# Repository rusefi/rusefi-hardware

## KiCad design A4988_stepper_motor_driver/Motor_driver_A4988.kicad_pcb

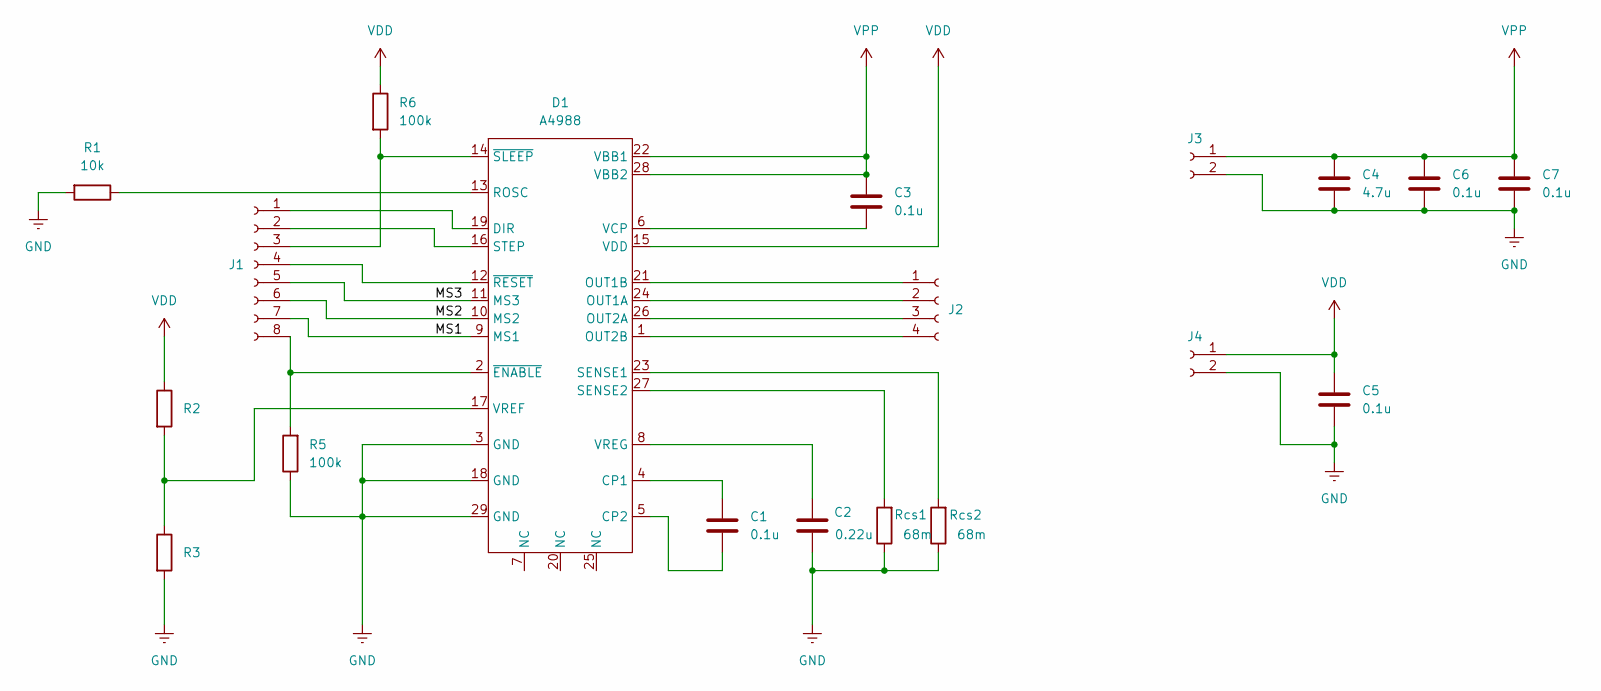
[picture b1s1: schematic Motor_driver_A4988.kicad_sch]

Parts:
C1, C3, C5, C6, C7: 0.1u; C_0603_1608Metric
C2: 0.22u; C_0603_1608Metric
C4: 4.7u; C_1206_3216Metric
D1: A4988; QFN-28-1EP_5x5mm_P0.5mm_EP3.35x3.35mm
J1: Conn_01x08_Socket; PinHeader_1x08_P2.54mm_Vertical
J2: Conn_01x04_Socket; PinHeader_1x04_P2.54mm_Vertical
J3, J4: Conn_01x02_Socket; PinHeader_1x02_P2.54mm_Vertical
R1: 10k; R_0603_1608Metric
R2, R3: R_0603_1608Metric
R5, R6: 100k; R_0603_1608Metric
Rcs1, Rcs2: 68m; R_1206_3216Metric

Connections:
/MS1: D1.9 (MS1), J1.7
/MS2: D1.10 (MS2), J1.6
/MS3: D1.11 (MS3), J1.5
GNDREF: C2.2, C4.2, C5.2, C6.2, C7.2, D1.3 (GND), D1.18 (GND), D1.29 (GND), J3.2, J4.2, R1.2, R3.2, R5.1, Rcs1.1, Rcs2.1
unnamed: C1.1, D1.4 (CP1)
unnamed: C1.2, D1.5 (CP2)
unnamed: D1.19 (DIR), J1.1
unnamed: D1.24 (OUT1A), J2.2
unnamed: D1.21 (OUT1B), J2.1
unnamed: D1.26 (OUT2A), J2.3
unnamed: D1.1 (OUT2B), J2.4
unnamed: D1.13 (ROSC), R1.1
unnamed: D1.23 (SENSE1), Rcs2.2
unnamed: D1.27 (SENSE2), Rcs1.2
unnamed: D1.16 (STEP), J1.2
unnamed: C3.2, D1.6 (VCP)
unnamed: D1.17 (VREF), R2.2, R3.1
unnamed: C2.1, D1.8 (VREG)
unnamed: D1.2 (~ENABLE), J1.8, R5.2
unnamed: D1.12 (~RESET), J1.4
unnamed: D1.14 (~SLEEP), J1.3, R6.2
VDD: C5.1, D1.15 (VDD), J4.1, R2.1, R6.1
VPP: C3.1, C4.1, C6.1, C7.1, D1.22 (VBB1), D1.28 (VBB2), J3.1

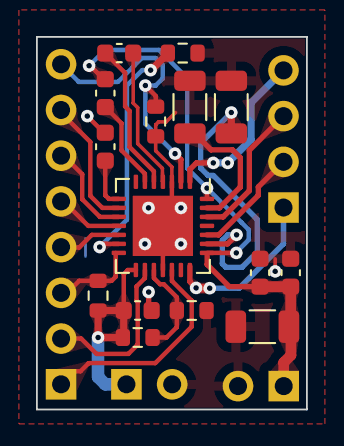
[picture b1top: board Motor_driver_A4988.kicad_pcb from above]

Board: 2 copper layers, 15.0 x 20.7 mm, 20 parts (1 on the bottom side), 23 nets.

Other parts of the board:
G?: LOGO

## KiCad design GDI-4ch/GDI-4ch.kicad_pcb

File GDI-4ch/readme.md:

[User Documentation](https://github.com/rusefi/rusefi/wiki/GDI4)

https://rusefi.com/forum/viewtopic.php?f=4&t=1337

## JLCPCB assembly

**DNP** means “do not place”: JLC will not install that whole group of parts. You solder them yourself later, or you fix the order before manufacturing so those spots get real parts from the JLC library. The DNP groups are listed in **`gerber/rev. c/GDI-4ch.csv`** — resistors **R1, R37, R44, R55, R80, R81, R82, R83, R87, R89, R90, R121** and **R5, R28, R30, R32, R117, R118, R119, R120**.

**If JLC is assembling the board for you:** In the online assembly step, check that you actually selected a part for every line you care about. Parts people often forget to turn on: diodes **D5 and D6** (JLC part number **C8678**), and the **0805 jumper pads** that share one line in the parts list (often **C17477** in **`gerber/rev. d/bom.csv`**). File names and lists change between revisions—use the **`gerber/`** folder that matches the board files you ordered.

## HOWTO Update Firmware

UART route https://www.adafruit.com/product/954

See also https://github.com/rusefi/rusefi/blob/master/firmware/controllers/lua/examples/gdi4-communication.lua

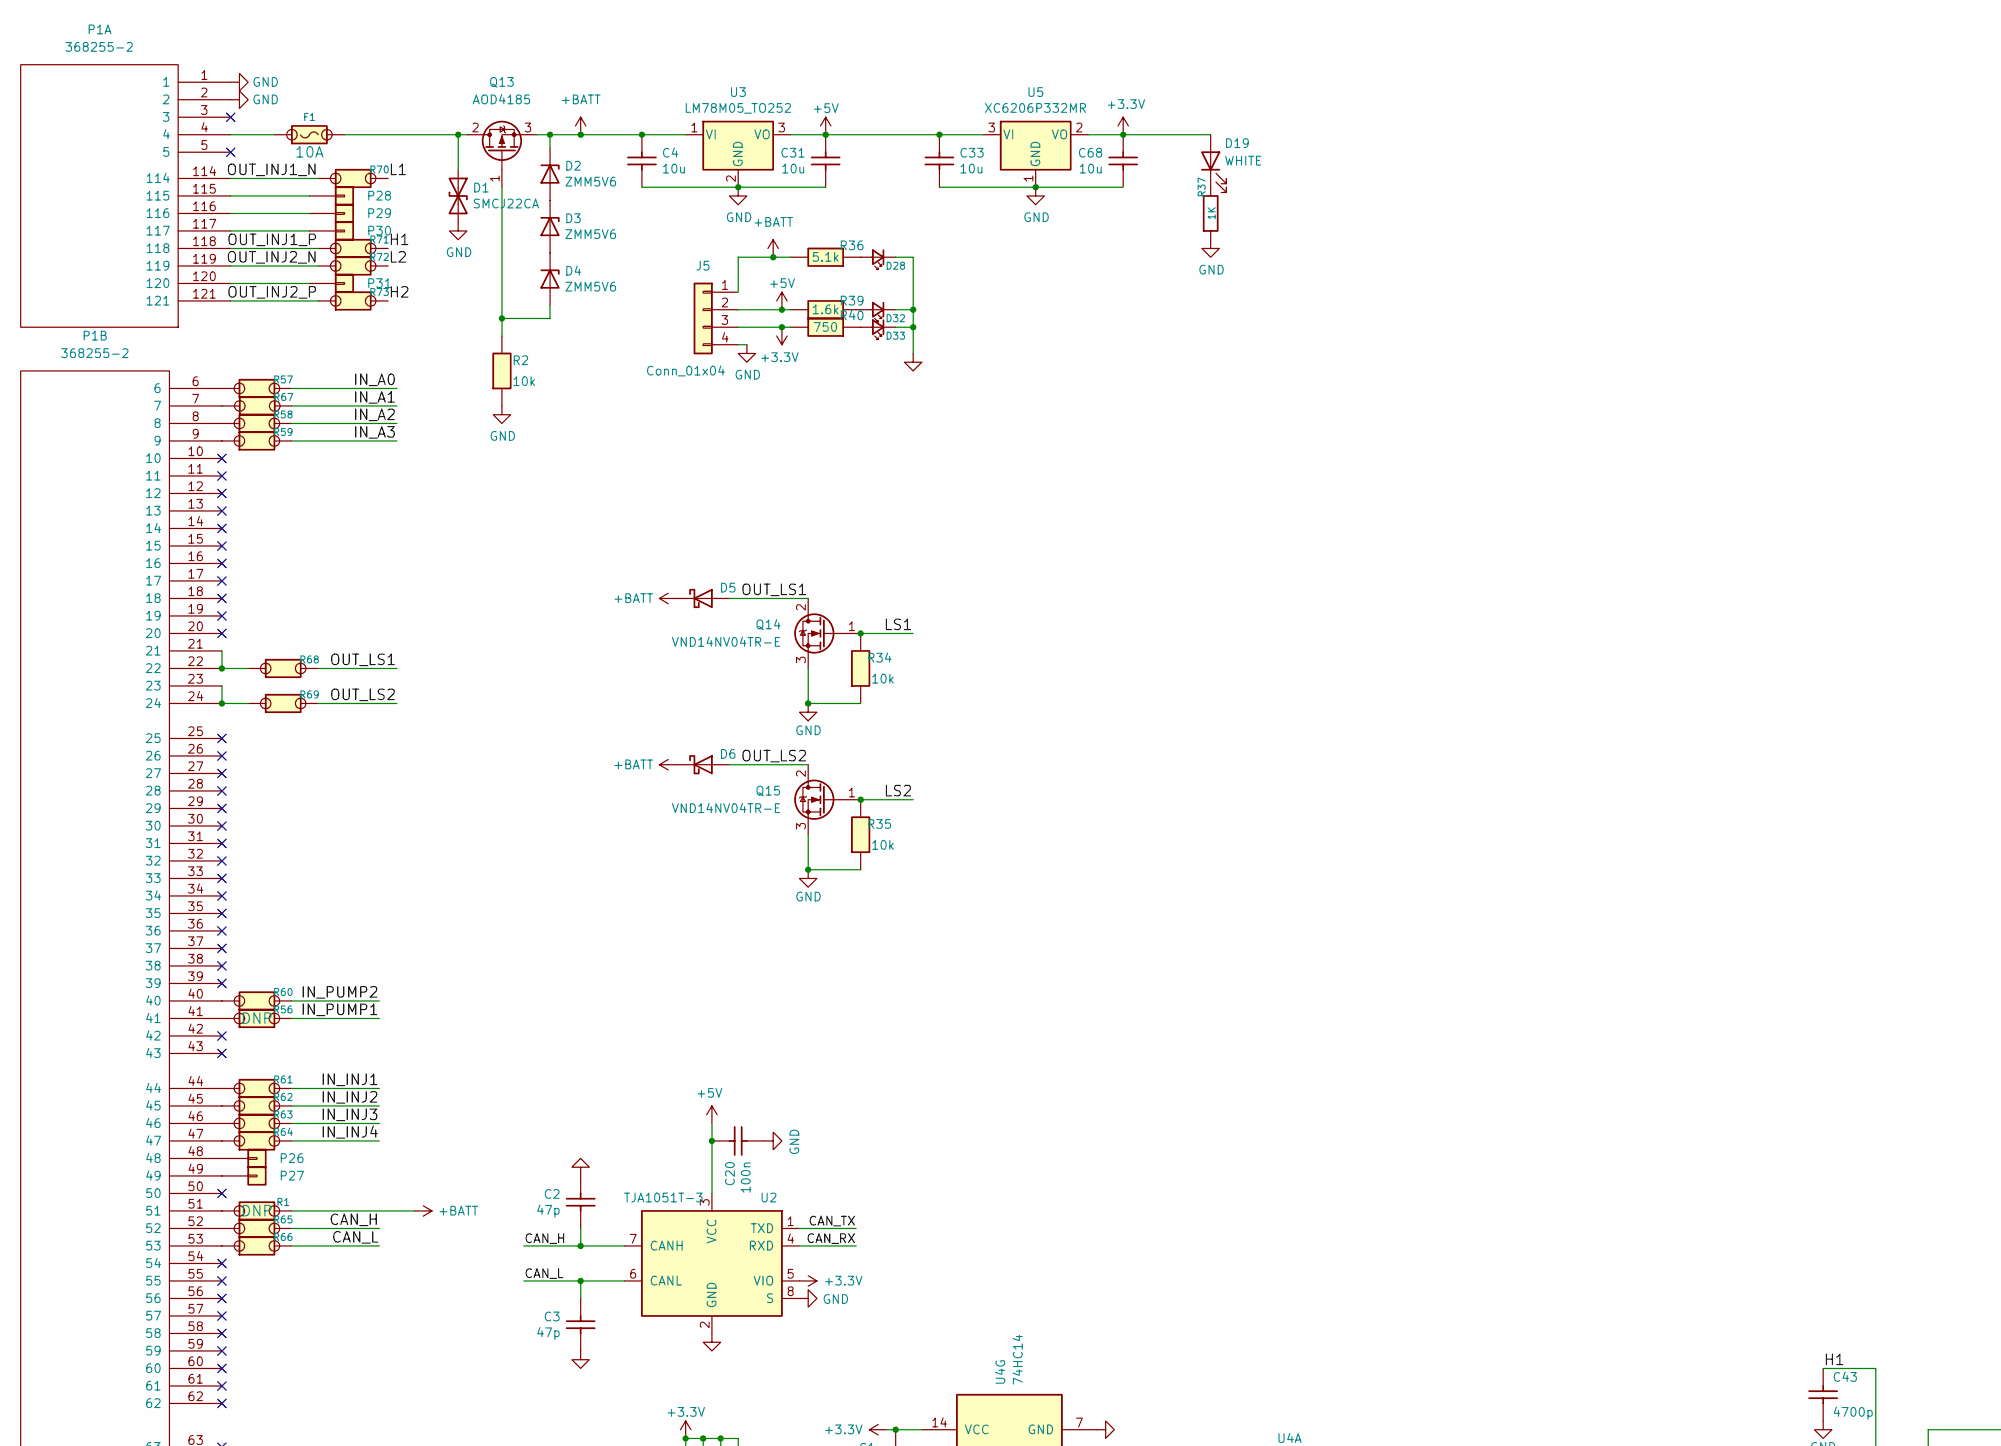
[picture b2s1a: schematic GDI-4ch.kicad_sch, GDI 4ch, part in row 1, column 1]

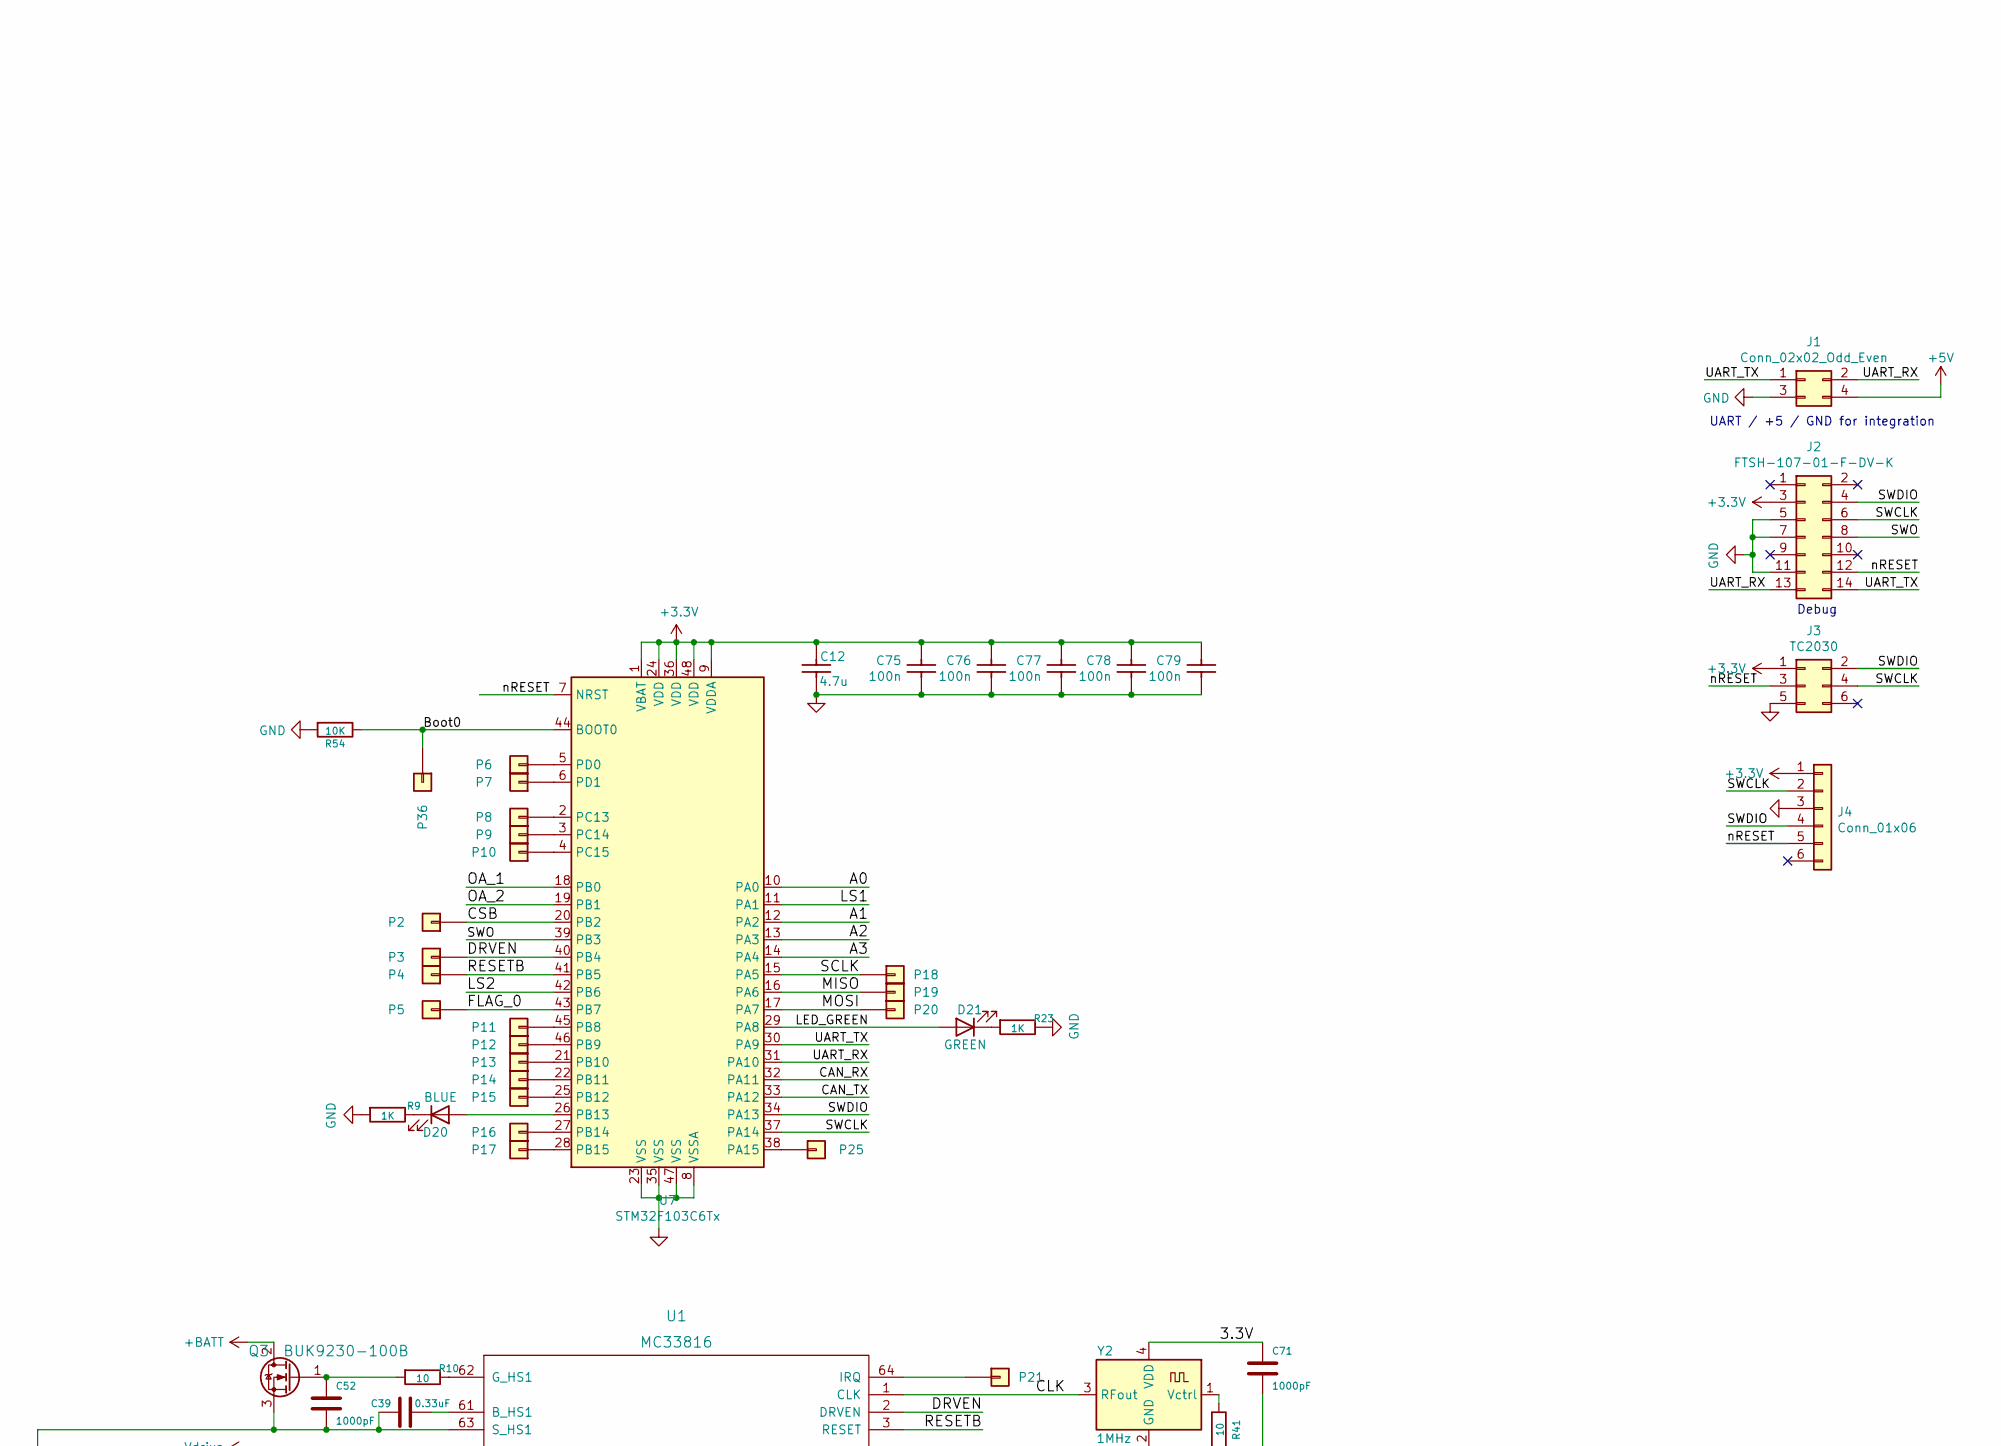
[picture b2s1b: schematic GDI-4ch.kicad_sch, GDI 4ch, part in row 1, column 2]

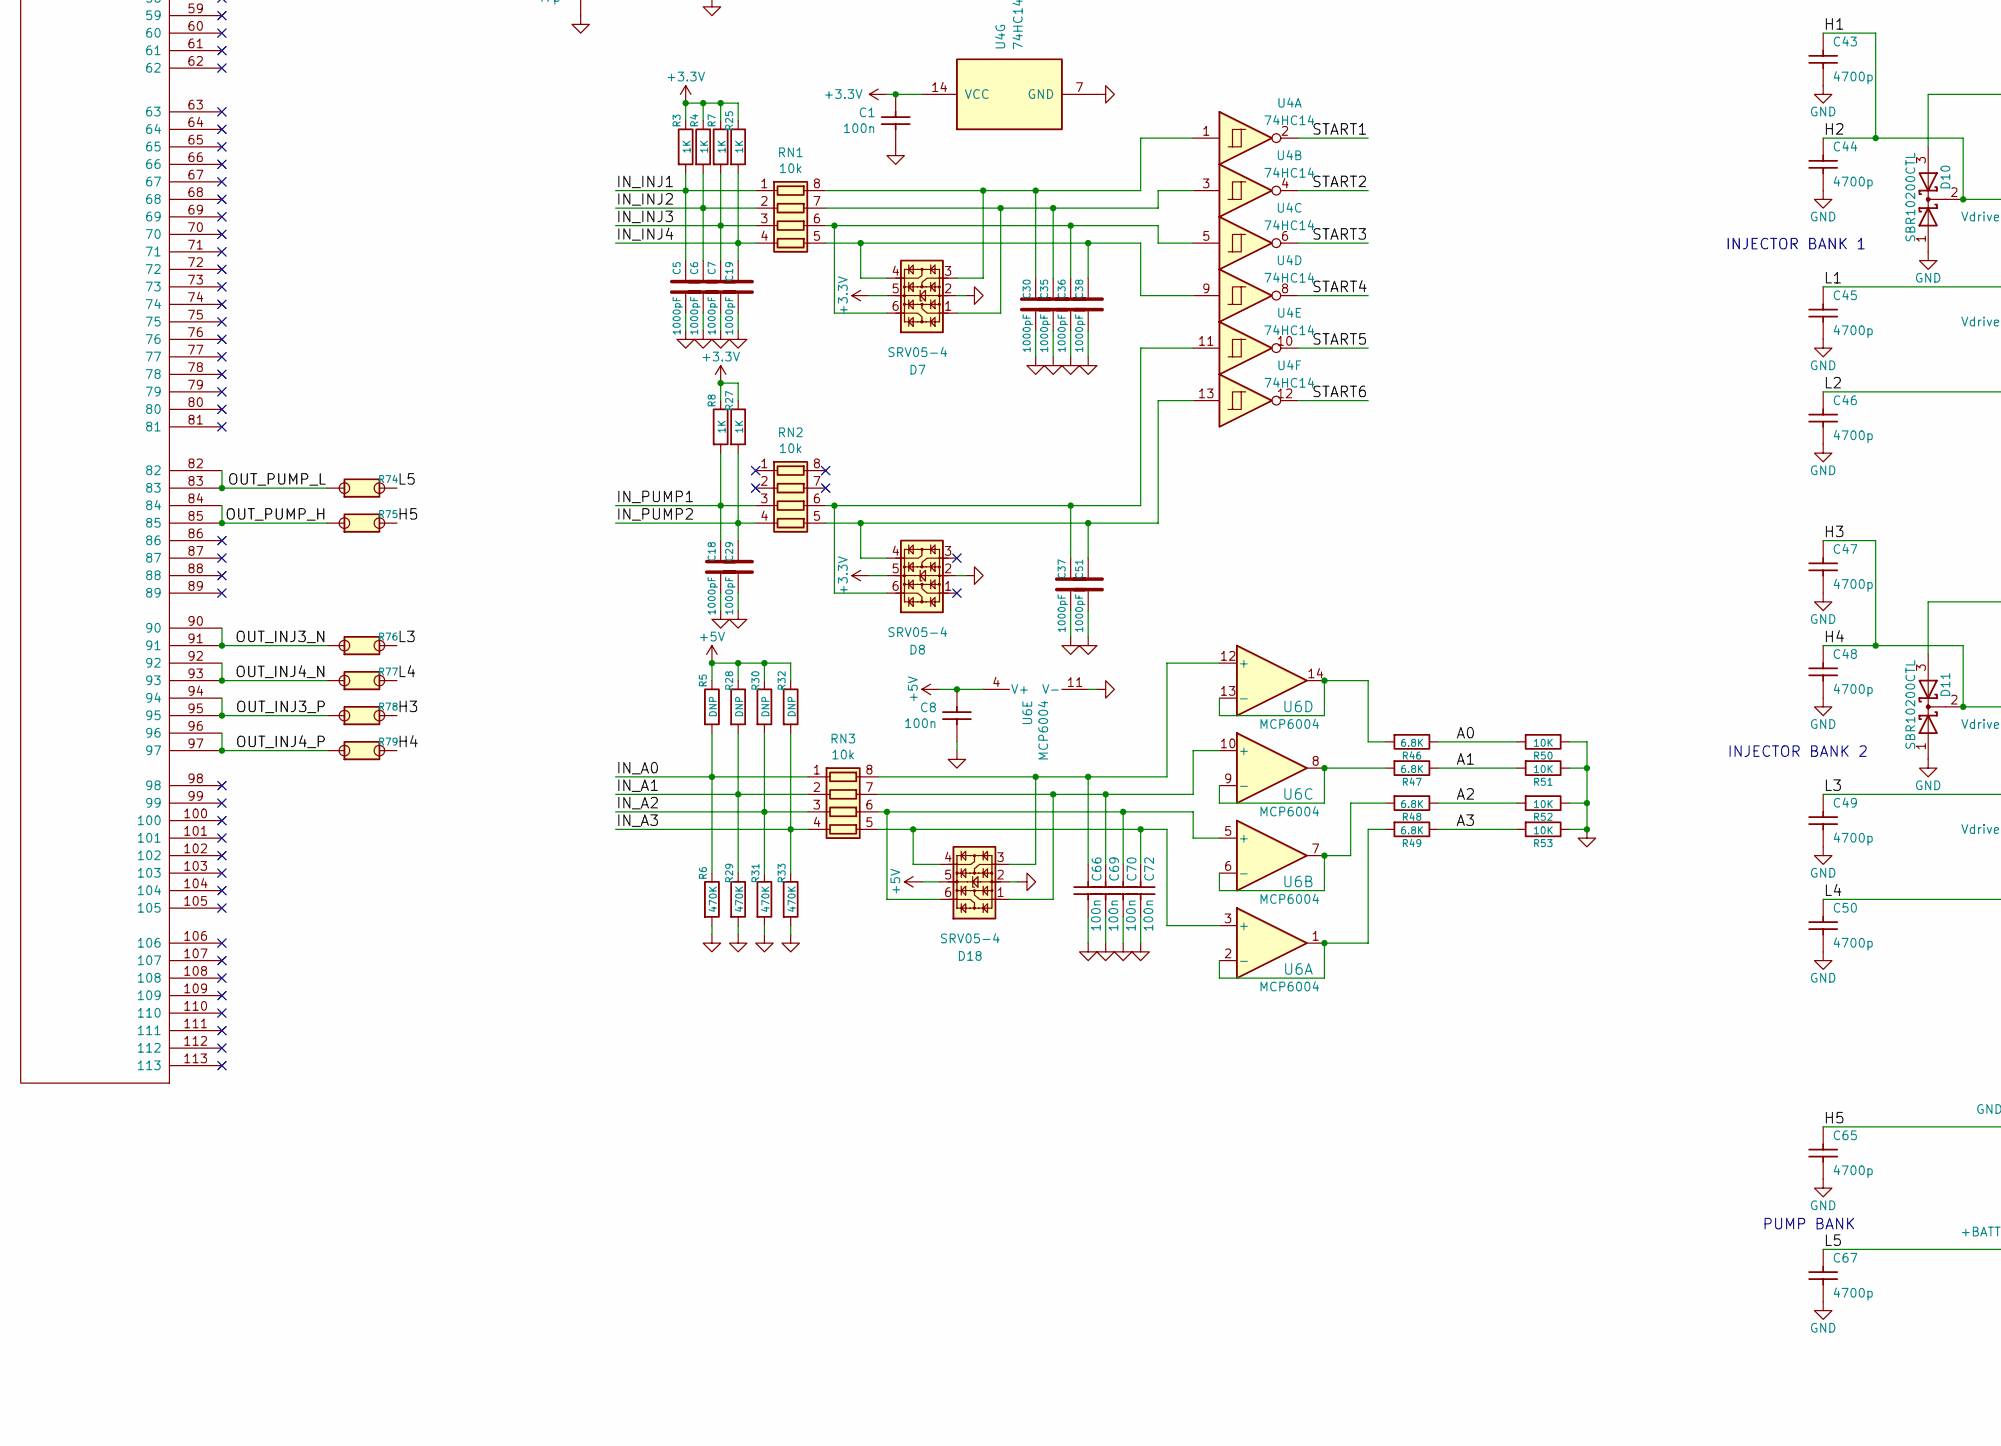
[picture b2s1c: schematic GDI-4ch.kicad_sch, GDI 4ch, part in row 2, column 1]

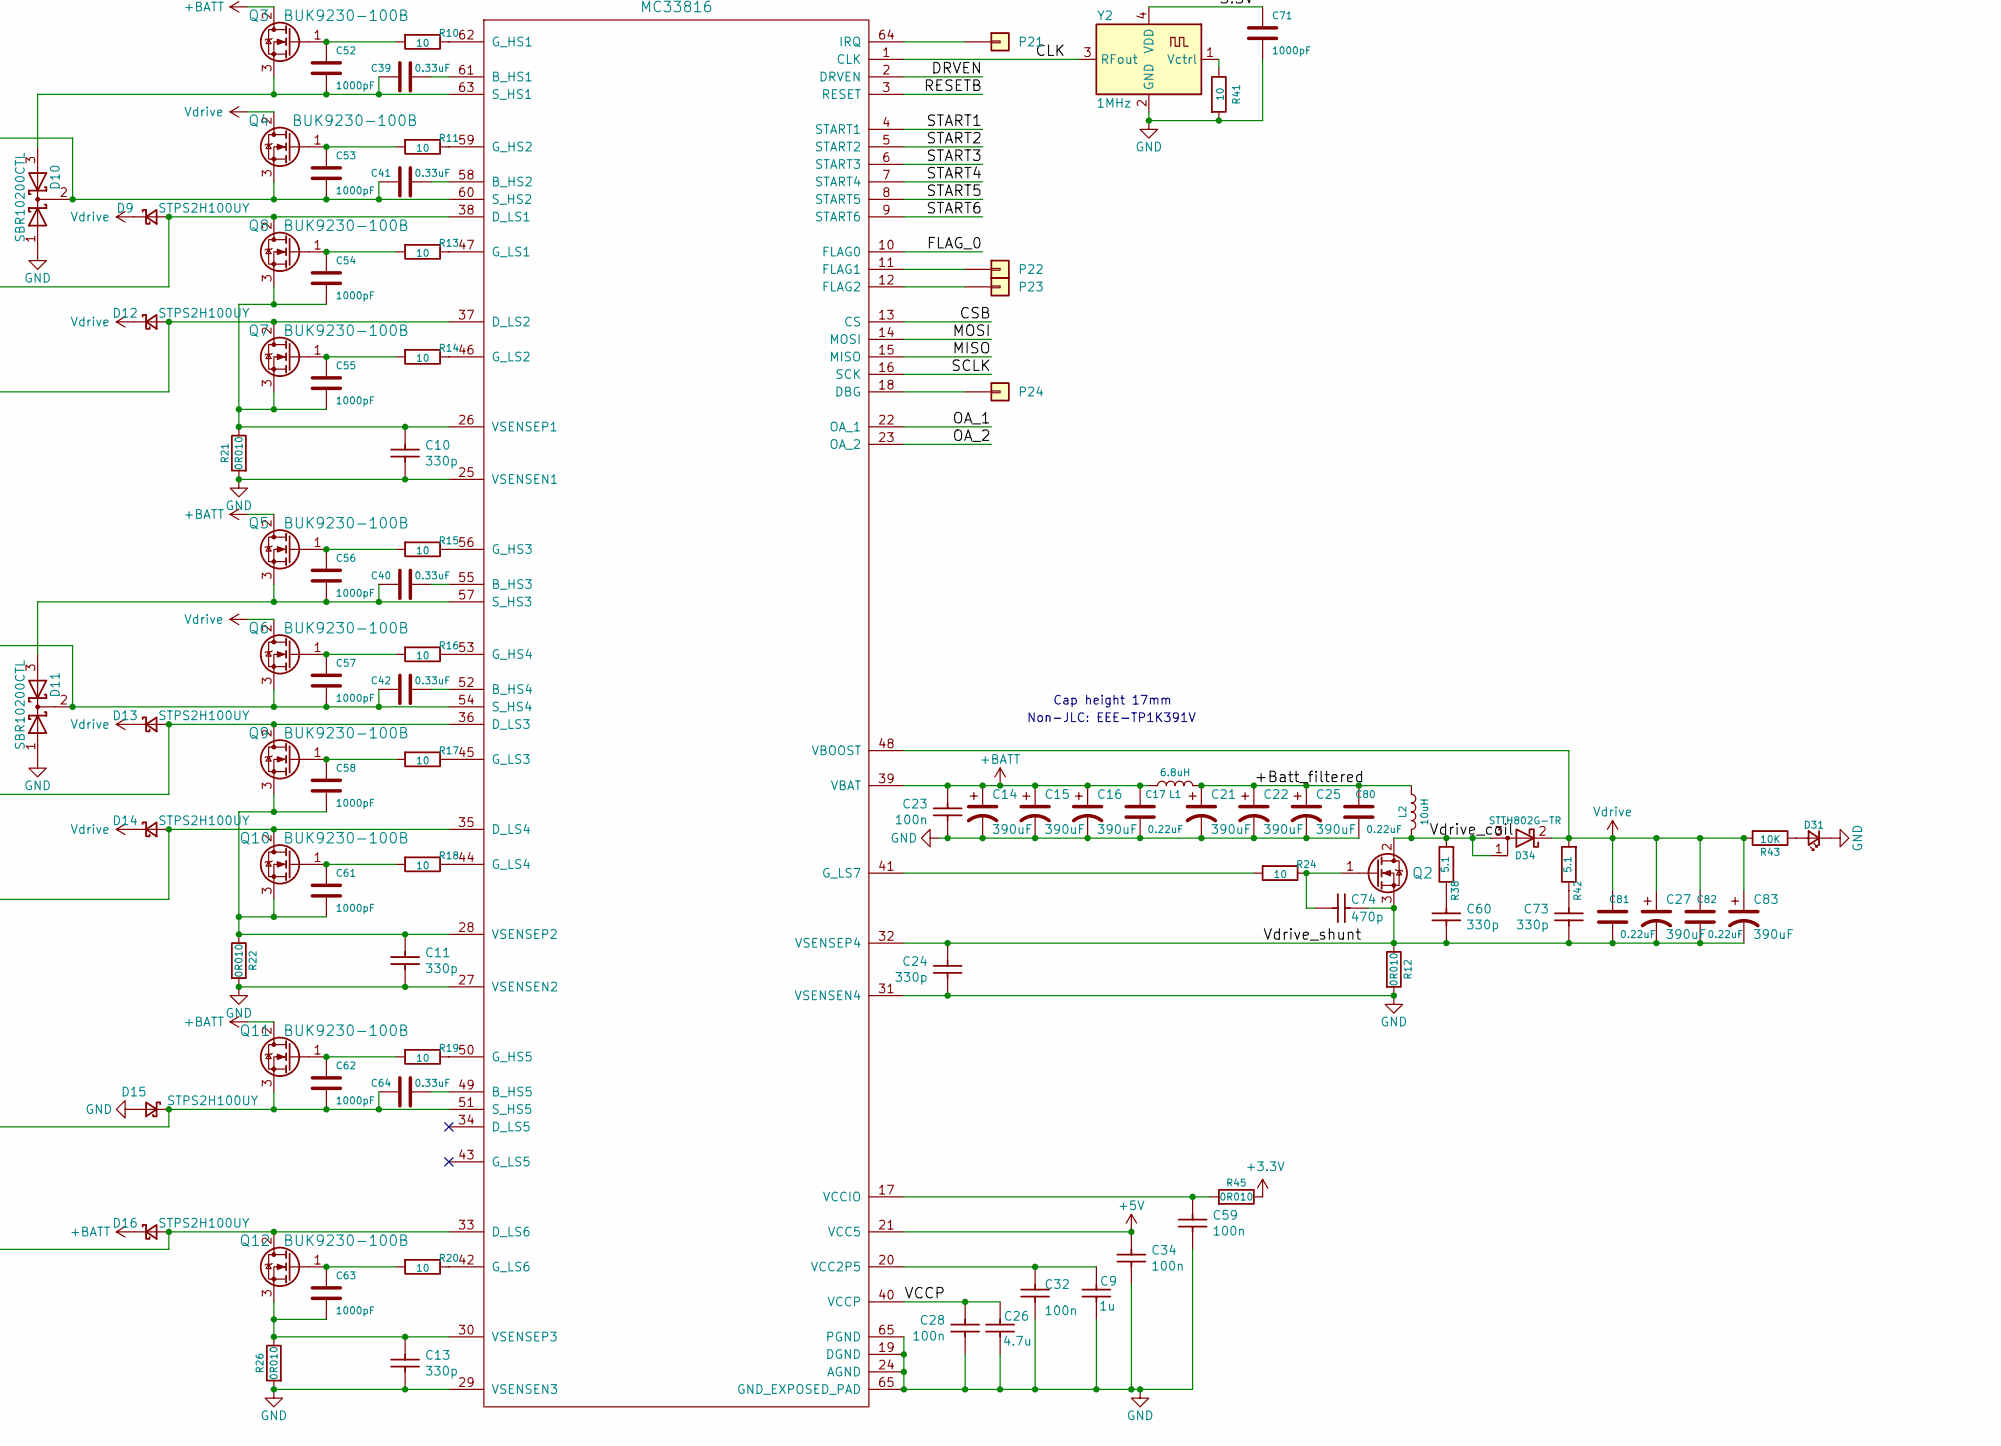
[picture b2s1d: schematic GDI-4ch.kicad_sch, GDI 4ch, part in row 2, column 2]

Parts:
C1, C8, C20, C23, C28, C32, C34, C59, C66, C69, C70, C72, C75, C76, C77, C78, C79: 100n; C0603; LCSC C14663
C2, C3: 47p; C0603; LCSC C1671
C4, C31, C33, C68: 10u; C_0805_2012Metric; LCSC C15850
C5, C6, C7, C18, C19, C29, C30, C35, C36, C37, C38, C51, C52, C53, C54, C55, C56, C57, C58, C61, C62, C63, C71: 1000pF; C_0603_1608Metric; LCSC C106247
C9: 1u; C0603; LCSC C15849
C10, C11, C13, C24, C60, C73: 330p; C0603; LCSC C576850
C12, C26: 4.7u; C0603; LCSC C19666
C14, C15, C16, C21, C22, C25, C27, C83: 390uF; CP_Elec_16x17.5; LCSC C487421
C17, C80, C81, C82: 0.22uF; C_0805_2012Metric; LCSC C342873
C39, C40, C41, C42, C64: 0.33uF; C_0603_1608Metric; LCSC C1615
C43, C44, C45, C46, C47, C48, C49, C50, C65, C67: 4700p; C0603; LCSC C342899
C74: 470p; C0603; LCSC C326973
D1: SMCJ22CA; D_SMC; LCSC C310038
D2, D3, D4: ZMM5V6; D_MiniMELF; LCSC C8062
D5, D6: D_Schottky; D_SMA; LCSC C8678
D7, D8, D18: SRV05-4; SOT-23-6; LCSC C85364
D9, D12, D13, D14, D15, D16: STPS2H100UY; D_SMB; LCSC C157420
D10, D11: SBR10200CTL; TO-252-2; LCSC C135494
D19: WHITE; LED_0603_1608Metric; LCSC C2290
D20: BLUE; LED_0603_1608Metric; LCSC C72041
D21: GREEN; LED_0603_1608Metric; LCSC C72043
D28, D31, D32, D33: LED_Small; LED_0805_2012Metric; LCSC C2296
D34: STTH802G-TR; TO-263-2; LCSC C181034
F1: Fuse-Pad-Pad; PAD-1206-PAD; LCSC C310989
J1: Conn_02x02_Odd_Even; PinHeader_2x02_P2.54mm_Vertical
J2: FTSH-107-01-F-DV-K; PinHeader_2x07_P1.27mm_Vertical_SMD
J3: TC2030; Tag-Connect_TC2030-IDC-NL_2x03_P1.27mm_Vertical
J4: Conn_01x06; PinHeader_1x06_P2.54mm_Vertical
J5: Conn_01x04; PinHeader_1x04_P2.54mm_Vertical
L1: 6.8uH; L_Wuerth_HCI-1350; LCSC C380073
L2: 10uH; L_Vishay_IHLP-6767; LCSC C237980
P1: 368255-2; TE_368255-2
P2, P3, P4, P5, P6, P7, P8, P9, P10, P11, P12, P13, P14, P15, P16, P17, P18, P19, P20, P21, P22, P23, P24, P25, P26, P27, P28, P29, P30, P31, P36: Pad; PAD-TH
Q2, Q3, Q4, Q5, Q6, Q7, Q8, Q9, Q10, Q11, Q12: BUK9230-100B; TO-252-2; LCSC C67277
Q13: AOD4185; TO-252-2; LCSC TO-252-2
Q14, Q15: VND14NV04TR-E; TO-252-2; LCSC C2649436
R1, R56: Jumper-Pad-Pad; PAD-0805-PAD
R2, R34, R35: 10k; R0603; LCSC C25804
R3, R4, R7, R8, R9, R23, R25, R27, R37: 1K; R_0603_1608Metric; LCSC C21190
R5, R28, R30, R32: DNP; R_0603_1608Metric
R6, R29, R31, R33: 470K; R_0603_1608Metric; LCSC C23178
R10, R11, R13, R14, R15, R16, R17, R18, R19, R20, R24, R41: 10; R_0603_1608Metric; LCSC C22859
R12, R21, R22, R26, R45: 0R010; R_1206_3216Metric_Pad1.30x1.75mm_HandSolder; LCSC C76294
R36: 5.1k; R0603; LCSC C23186
R38, R42: 5.1; R_0603_1608Metric; LCSC C25197
R39: 1.6k; R0603; LCSC C22847
R40: 750; R0603; LCSC C23241
R43, R50, R51, R52, R53, R54: 10K; R_0603_1608Metric; Part # RMCF0603JT10K0; LCSC C25804
R46, R47, R48, R49: 6.8K; R_0603_1608Metric; LCSC C23212
R57, R58, R59, R60, R61, R62, R63, R64, R65, R66, R67, R68, R69, R70, R71, R72, R73, R74, R75, R76, R77, R78, R79: Jumper-Pad-Pad; PAD-0805-PAD; LCSC C17477
RN1, RN2, RN3: 10k; R_Array_Convex_4x0603; Part # YC164-JR-0710KL; LCSC C29718
U1: MC33816; LQFP-64-1EP_10x10mm_P0.5mm_EP5x5mm_ThermalVias
U2: TJA1051T-3; SOIC-8_3.9x4.9mm_P1.27mm; LCSC C38695
U3: LM78M05_TO252; TO-252-2; LCSC C58069
U4: 74HC14; TSSOP-14_4.4x5mm_P0.65mm
U5: XC6206P332MR; SOT-23; LCSC C5446
U6: MCP6004; TSSOP-14_4.4x5mm_P0.65mm; Part # MCP6004T-I/ST; LCSC C248577
U7: STM32F103C6Tx; LQFP-48_7x7mm_P0.5mm; LCSC C8303
Y2: 1MHz; Oscillator_SMD_Diodes_FN-4Pin_7.0x5.0mm; LCSC C70608

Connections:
+3V3: C1.2, C12.2, C68.2, C75.2, C76.2, C77.2, C78.2, C79.2, D7.5, D8.5, D19.2 (A), J2.3, J3.1, J4.1, J5.3, R3.1, R4.1, R7.1, R8.1, R25.1, R27.1, R40.2, R45.1, U2.5 (VIO), U4.14 (VCC), U5.2 (VO), U7.1 (VBAT), U7.9 (VDDA), U7.24 (VDD), U7.36 (VDD), U7.48 (VDD)
+5V: C8.2, C20.2, C31.2, C33.2, C34.2, D18.5, J1.4, J5.2, R5.1, R28.1, R30.1, R32.1, R39.2, U1.21 (VCC5), U2.3 (VCC), U3.3 (VO), U5.3 (VI), U6.4 (V+)
+BATT: C4.2, C14.1, C15.1, C16.1, C17.1, C23.2, D2.1 (K), D5.1 (K), D6.1 (K), D16.1 (K), J5.1, L1.1, Q3.2 (D), Q5.2 (D), Q11.2 (D), Q13.3 (S), R1.2, R36.2, U1.39 (VBAT), U3.1 (VI)
/3.3V: C71.2, Y2.4 (VDD)
/+Batt_filtered: C21.1, C22.1, C25.1, C80.1, L1.2, L2.1
/A0: R46.1, R50.2, U7.10 (PA0)
/A1: R47.1, R51.2, U7.12 (PA2)
/A2: R48.1, R52.2, U7.13 (PA3)
/A3: R49.1, R53.2, U7.14 (PA4)
/Boot0: P36.1, R54.1, U7.44 (BOOT0)
/CAN_H: C2.1, R65.2, U2.7 (CANH)
/CAN_L: C3.2, R66.2, U2.6 (CANL)
/CAN_RX: U2.4 (RXD), U7.32 (PA11)
/CAN_TX: U2.1 (TXD), U7.33 (PA12)
/CLK: U1.1 (CLK), Y2.3 (RFout)
/CSB: P2.1, U1.13 (CS), U7.20 (PB2)
/DRVEN: P3.1, U1.2 (DRVEN), U7.40 (PB4)
/FLAG_0: P5.1, U1.10 (FLAG0), U7.43 (PB7)
/H1: C41.2, C43.2, C44.2, C53.1, D10.2 (K), Q4.3 (S), R71.2, R73.2, U1.60 (S_HS2)
/H3: C42.2, C47.2, C48.2, C57.1, D11.2 (K), Q6.3 (S), R78.2, R79.2, U1.54 (S_HS4)
/H5: C62.1, C64.2, C65.2, D15.1 (K), Q11.3 (S), R75.2, U1.51 (S_HS5)
/IN_A0: R5.2, R6.1, R57.2, RN3.1 (R1.1)
/IN_A1: R28.2, R29.1, R67.2, RN3.2 (R2.1)
/IN_A2: R30.2, R31.1, R58.2, RN3.3 (R3.1)
/IN_A3: R32.2, R33.1, R59.2, RN3.4 (R4.1)
/IN_INJ1: C5.2, R3.2, R61.2, RN1.1 (R1.1)
/IN_INJ2: C6.2, R4.2, R62.2, RN1.2 (R2.1)
/IN_INJ3: C7.2, R7.2, R63.2, RN1.3 (R3.1)
/IN_INJ4: C19.2, R25.2, R64.2, RN1.4 (R4.1)
/IN_PUMP1: C18.2, R8.2, R56.2, RN2.3 (R3.1)
/IN_PUMP2: C29.2, R27.2, R60.2, RN2.4 (R4.1)
/L1: C45.2, D9.2 (A), Q8.2 (D), R70.2, U1.38 (D_LS1)
/L2: C46.2, D12.2 (A), Q7.2 (D), R72.2, U1.37 (D_LS2)
/L3: C49.2, D13.2 (A), Q9.2 (D), R76.2, U1.36 (D_LS3)
/L4: C50.2, D14.2 (A), Q10.2 (D), R77.2, U1.35 (D_LS4)
/L5: C67.2, D16.2 (A), Q12.2 (D), R74.2, U1.33 (D_LS6)
/LED_GREEN: D21.2 (A), U7.29 (PA8)
/LS1: Q14.1 (G), R34.2, U7.11 (PA1)
/LS2: Q15.1 (G), R35.2, U7.42 (PB6)
/MISO: P19.1, U1.15 (MISO), U7.16 (PA6)
/MOSI: P20.1, U1.14 (MOSI), U7.17 (PA7)
/OA_1: U1.22 (OA_1), U7.18 (PB0)
/OA_2: U1.23 (OA_2), U7.19 (PB1)
/OUT_INJ1_N: P1.114, R70.1
/OUT_INJ1_P: P1.118, R71.1
/OUT_INJ2_N: P1.119, R72.1
/OUT_INJ2_P: P1.121, R73.1
/OUT_INJ3_N: P1.90, P1.91, R76.1
/OUT_INJ3_P: P1.94, P1.95, R78.1
/OUT_INJ4_N: P1.92, P1.93, R77.1
/OUT_INJ4_P: P1.96, P1.97, R79.1
/OUT_LS1: D5.2 (A), Q14.2 (D), R68.2
/OUT_LS2: D6.2 (A), Q15.2 (D), R69.2
/OUT_PUMP_H: P1.84, P1.85, R75.1
/OUT_PUMP_L: P1.82, P1.83, R74.1
/RESETB: P4.1, U1.3 (RESET), U7.41 (PB5)
/SCLK: P18.1, U1.16 (SCK), U7.15 (PA5)
/START1: U1.4 (START1), U4.2
/START2: U1.5 (START2), U4.4
/START3: U1.6 (START3), U4.6
/START4: U1.7 (START4), U4.8
/START5: U1.8 (START5), U4.10
/START6: U1.9 (START6), U4.12
/SWCLK: J2.6, J3.4, J4.2, U7.37 (PA14)
/SWDIO: J2.4, J3.2, J4.4, U7.34 (PA13)
/SWO: J2.8, U7.39 (PB3)
/UART_RX: J1.2, J2.13, U7.31 (PA10)
/UART_TX: J1.1, J2.14, U7.30 (PA9)
/VCCP: C26.2, C28.2, U1.40 (VCCP)
/Vdrive_coil: D34.1 (A), D34.3 (A), L2.2, Q2.2 (D), R38.2
/Vdrive_shunt: C24.2, C27.2, C60.1, C73.1, C74.1, C81.2, C82.2, C83.2, Q2.3 (S), R12.1, U1.32 (VSENSEP4)
/nRESET: J2.12, J3.3, J4.5, U7.7 (NRST)
GND: C1.1, C2.2, C3.1, C4.1, C5.1, C6.1, C7.1, C8.1, C9.1, C10.1, C11.1, C12.1, C13.1, C14.2, C15.2, C16.2, C17.2, C18.1, C19.1, C20.1, C21.2, C22.2, C23.1, C24.1, C25.2, C26.1, C28.1, C29.1, C30.1, C31.1, C32.1, C33.1, C34.1, C35.1, C36.1, C37.1, C38.1, C43.1, C44.1, C45.1, C46.1, C47.1, C48.1, C49.1, C50.1, C51.1, C59.1, C65.1, C66.1, C67.1, C68.1, C69.1, C70.1, C71.1, C72.1, C75.1, C76.1, C77.1, C78.1, C79.1, C80.2, D1.2 (A2), D7.2, D8.2, D10.1 (A), D11.1 (A), D15.2 (A), D18.2, D28.1 (K), D31.1 (K), D32.1 (K), D33.1 (K), J1.3, J2.5, J2.7, J2.11, J3.5, J4.3, J5.4, P1.1, P1.2, Q14.3 (S), Q15.3 (S), R2.1, R6.2, R9.2, R12.2, R21.2, R22.2, R23.1, R26.2, R29.2, R31.2, R33.2, R34.1, R35.1, R37.2, R41.2, R50.1, R51.1, R52.1, R53.1, R54.2, U1.19 (DGND), U1.24 (AGND), U1.25 (VSENSEN1), U1.27 (VSENSEN2), U1.29 (VSENSEN3), U1.31 (VSENSEN4), U1.65 (PGND), U2.2 (GND), U2.8 (S), U3.2 (GND), U4.7 (GND), U5.1 (GND), U6.11 (V-), U7.8 (VSSA), U7.23 (VSS), U7.35 (VSS), U7.47 (VSS), Y2.2 (GND)
unnamed: C10.2, C54.1, C55.1, Q7.3 (S), Q8.3 (S), R21.1, U1.26 (VSENSEP1)
unnamed: C11.2, C58.1, C61.1, Q9.3 (S), Q10.3 (S), R22.1, U1.28 (VSENSEP2)
unnamed: C13.2, C63.1, Q12.3 (S), R26.1, U1.30 (VSENSEP3)
unnamed: C30.2, D7.3, RN1.8 (R1.2), U4.1
unnamed: C9.2, C32.2, U1.20 (VCC2P5)
unnamed: C35.2, D7.1, RN1.7 (R2.2), U4.3
unnamed: C36.2, D7.6, RN1.6 (R3.2), U4.5
unnamed: C37.2, D8.6, RN2.6 (R3.2), U4.11
unnamed: C38.2, D7.4, RN1.5 (R4.2), U4.9
unnamed: C39.1, U1.61 (B_HS1)
unnamed: C39.2, C52.1, D10.3 (A), Q3.3 (S), U1.63 (S_HS1)
unnamed: C40.1, U1.55 (B_HS3)
unnamed: C40.2, C56.1, D11.3 (A), Q5.3 (S), U1.57 (S_HS3)
unnamed: C41.1, U1.58 (B_HS2)
unnamed: C42.1, U1.52 (B_HS4)
unnamed: C51.2, D8.4, RN2.5 (R4.2), U4.13
unnamed: C52.2, Q3.1 (G), R10.2
unnamed: C53.2, Q4.1 (G), R11.2
unnamed: C54.2, Q8.1 (G), R13.2
unnamed: C55.2, Q7.1 (G), R14.2
unnamed: C56.2, Q5.1 (G), R15.2
unnamed: C57.2, Q6.1 (G), R16.2
unnamed: C58.2, Q9.1 (G), R17.2
unnamed: C59.2, R45.2, U1.17 (VCCIO)
unnamed: C60.2, R38.1
unnamed: C61.2, Q10.1 (G), R18.2
unnamed: C62.2, Q11.1 (G), R19.2
unnamed: C63.2, Q12.1 (G), R20.2
unnamed: C64.1, U1.49 (B_HS5)
unnamed: C73.2, R42.1
unnamed: C74.2, Q2.1 (G), R24.1
unnamed: D1.1 (A1), F1.2, Q13.2 (D)
unnamed: D2.2 (A), D3.1 (K)
unnamed: D3.2 (A), D4.1 (K)
unnamed: D4.2 (A), Q13.1 (G), R2.2
unnamed: C69.2, D18.1, RN3.7 (R2.2), U6.10 (+)
unnamed: C66.2, D18.3, RN3.8 (R1.2), U6.12 (+)
unnamed: C72.2, D18.4, RN3.5 (R4.2), U6.3 (+)
unnamed: C70.2, D18.6, RN3.6 (R3.2), U6.5 (+)
unnamed: D19.1 (K), R37.1
unnamed: D20.1 (K), R9.1
unnamed: D20.2 (A), U7.26 (PB13)
unnamed: D21.1 (K), R23.2
unnamed: D28.2 (A), R36.1
unnamed: D32.2 (A), R39.1
unnamed: D33.2 (A), R40.1
unnamed: F1.1, P1.4
unnamed: P1.6, R57.1
unnamed: P1.7, R67.1
unnamed: P1.8, R58.1
unnamed: P1.9, R59.1
unnamed: P1.21, P1.22, R68.1
unnamed: P1.23, P1.24, R69.1
unnamed: P1.40, R60.1
unnamed: P1.41, R56.1
unnamed: P1.44, R61.1
unnamed: P1.45, R62.1
unnamed: P1.46, R63.1
unnamed: P1.47, R64.1
unnamed: P1.48, P26.1
unnamed: P1.49, P27.1
unnamed: P1.51, R1.1
unnamed: P1.52, R65.1
unnamed: P1.53, R66.1
unnamed: P1.115, P28.1
unnamed: P1.116, P29.1
unnamed: P1.117, P30.1
unnamed: P1.120, P31.1
unnamed: P6.1, U7.5 (PD0)
unnamed: P7.1, U7.6 (PD1)
unnamed: P8.1, U7.2 (PC13)
unnamed: P9.1, U7.3 (PC14)
unnamed: P10.1, U7.4 (PC15)
unnamed: P11.1, U7.45 (PB8)
unnamed: P12.1, U7.46 (PB9)
unnamed: P13.1, U7.21 (PB10)
unnamed: P14.1, U7.22 (PB11)
unnamed: P15.1, U7.25 (PB12)
unnamed: P16.1, U7.27 (PB14)
unnamed: P17.1, U7.28 (PB15)
unnamed: P21.1, U1.64 (IRQ)
unnamed: P22.1, U1.11 (FLAG1)
unnamed: P23.1, U1.12 (FLAG2)
unnamed: P24.1, U1.18 (DBG)
unnamed: P25.1, U7.38 (PA15)
unnamed: R10.1, U1.62 (G_HS1)
unnamed: R11.1, U1.59 (G_HS2)
unnamed: R13.1, U1.47 (G_LS1)
unnamed: R14.1, U1.46 (G_LS2)
unnamed: R15.1, U1.56 (G_HS3)
unnamed: R16.1, U1.53 (G_HS4)
unnamed: R17.1, U1.45 (G_LS3)
unnamed: R18.1, U1.44 (G_LS4)
unnamed: R19.1, U1.50 (G_HS5)
unnamed: R20.1, U1.42 (G_LS6)
unnamed: R24.2, U1.41 (G_LS7)
unnamed: R41.1, Y2.1 (Vctrl)
unnamed: D31.2 (A), R43.1
unnamed: R46.2, U6.13 (-), U6.14
unnamed: R47.2, U6.8, U6.9 (-)
unnamed: R48.2, U6.6 (-), U6.7
unnamed: R49.2, U6.1, U6.2 (-)
Vdrive: C27.1, C81.1, C82.1, C83.1, D9.1 (K), D12.1 (K), D13.1 (K), D14.1 (K), D34.2 (K), Q4.2 (D), Q6.2 (D), R42.2, R43.2, U1.48 (VBOOST)

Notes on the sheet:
INJECTOR BANK 1
Non-JLC: EEE-TP1K391V
Cap height 17mm
PUMP BANK
Debug
INJECTOR BANK 2
UART / +5 / GND for integration

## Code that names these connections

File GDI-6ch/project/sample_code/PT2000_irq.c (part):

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            if (inj1_error > auto_retry)  // Shutdown INJ1
            {
                send_single_PT2000_SPI_Cmd(WRITE, ch1_ctrl_reg_uc0, 0x40); // Clear the fault by writing the control register b6
                flag_start1_fail = 1;  // Put start1 flag high in order to stop Start1 pulse
            }
            else
            {
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            if (inj2_error > auto_retry)  // Shutdown INJ1
            {
                send_single_PT2000_SPI_Cmd(WRITE, ch1_ctrl_reg_uc0, 0x40); // Clear the fault by writing the control register b6
                flag_start2_fail = 1;  // Put start1 flag high in order to stop Start2 pulse
            }
            else
            {
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            if (inj3_error > auto_retry)    // Shutdown INJ1
            {
                send_single_PT2000_SPI_Cmd(WRITE, ch1_ctrl_reg_uc1, 0x40); // Clear the fault by writing the control register
                flag_start3_fail = 1;                                      // Put start1 flag high in order to stop Start3 pulse
            }
            else
            {
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            if (inj4_error > auto_retry)    // Shutdown INJ1
            {
                send_single_PT2000_SPI_Cmd(WRITE, ch1_ctrl_reg_uc1, 0x40); // Clear the fault by writing the control register
                flag_start4_fail = 1;                                      // Put start1 flag high in order to stop Start4 pulse
            }
            else
            {
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            if (inj5_error > auto_retry)    // Shutdown INJ5
            {
                send_single_PT2000_SPI_Cmd(WRITE, ch2_ctrl_reg_uc0, 0x40); // Clear the fault by writing the control register
                flag_start5_fail = 1;                                      // Put start1 flag high in order to stop Start5 pulse
            }
            else
            {
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            if (inj6_error > auto_retry)    // Shutdown INJ6
            {
                send_single_PT2000_SPI_Cmd(WRITE, ch2_ctrl_reg_uc0, 0x40); // Clear the fault by writing the control register
                flag_start6_fail = 1;                                      // Put start1 flag high in order to stop Start6 pulse
            }
            else
            {
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            if (fp_error > auto_retry)    // Shutdown FP
            {
                send_single_PT2000_SPI_Cmd(WRITE, ch3_ctrl_reg_uc0, 0x40); // Clear the fault by writing the control register
                flag_start7_fail = 1;                                      // Put start1 flag high in order to stop Start7 pulse
            }
            else
            {
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            if (inj1_error > sw_retry)  // Shutdown INJ1
            {
                send_single_PT2000_SPI_Cmd(WRITE, ch1_ctrl_reg_uc0, 0x1A0); // Clear the fault by writing the control register
                flag_start1_fail = 1;                                       // Put start1 flag high in order to stop Start1 pulse
            }
            else
            {
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            if (inj2_error > sw_retry)  // Shutdown INJ2
            {
                send_single_PT2000_SPI_Cmd(WRITE, ch1_ctrl_reg_uc0, 0x1A0); // Clear the fault by writing the control register
                flag_start2_fail = 1;                                       // Put start1 flag high in order to stop Start2 pulse
            }
            else
            {
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            if (inj3_error > sw_retry)  // Shutdown INJ3
            {
                send_single_PT2000_SPI_Cmd(WRITE, ch1_ctrl_reg_uc1, 0x1A0);  // Clear the fault by writing the control register
                flag_start3_fail = 1;                                        // Put start1 flag high in order to stop Start3 pulse
            }
            else
            {
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            if (inj4_error > sw_retry)  // Shutdown INJ4
            {
                send_single_PT2000_SPI_Cmd(WRITE, ch1_ctrl_reg_uc1, 0x1A0);  // Clear the fault by writing the control register
                flag_start4_fail = 1;                                        // Put start1 flag high in order to stop Start4 pulse
            }
            else
            {
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            if (inj5_error > sw_retry)  // Shutdown INJ5
            {
                send_single_PT2000_SPI_Cmd(WRITE, ch2_ctrl_reg_uc0, 0x1A0); // Clear the fault by writing the control register
                flag_start5_fail = 1;                                       // Put start1 flag high in order to stop Start5 pulse
            }
            else
            {
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            if (inj6_error > sw_retry)  // Shutdown INJ6
            {
                send_single_PT2000_SPI_Cmd(WRITE, ch2_ctrl_reg_uc0, 0x1A0); // Clear the fault by writing the control register
                flag_start6_fail = 1;                                       // Put start1 flag high in order to stop Start6 pulse
            }
            else
            {
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            if (fp_error > sw_retry)  // Shutdown INJ3
            {
                send_single_PT2000_SPI_Cmd(WRITE, ch3_ctrl_reg_uc0, 0x1A0); // Clear the fault by writing the control register
                flag_start7_fail = 1;                                       // Put start1 flag high in order to stop Start7 pulse
            }
            else
            {
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            dcdc_error++;
            if (dcdc_error > sw_retry)  // Shutdown DCDC and all injections
            {
                // ConfigureGPIO(PORTB,  8, PTB, GPIO_INPUT_DIRECTION);  // START1 force as INPUT so low...
            }
            else
            {
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    unsigned char HS_Boost_error=0;
    unsigned char HS_Bat_error=0;
    unsigned char LS_error=0;
    unsigned int Fault_signature=0;            //0 no fault, 1 Short to GND, 2 Short to Bat, 4 INJ Open, 8 MOSFET Open
    unsigned int HSxData;
    unsigned int LSxData;
    _Bool FuelPump =0;
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

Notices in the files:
GDI-6ch/project/sample_code/PT2000_irq.c:
Copyright(C) 2025 NXP Semiconductors
